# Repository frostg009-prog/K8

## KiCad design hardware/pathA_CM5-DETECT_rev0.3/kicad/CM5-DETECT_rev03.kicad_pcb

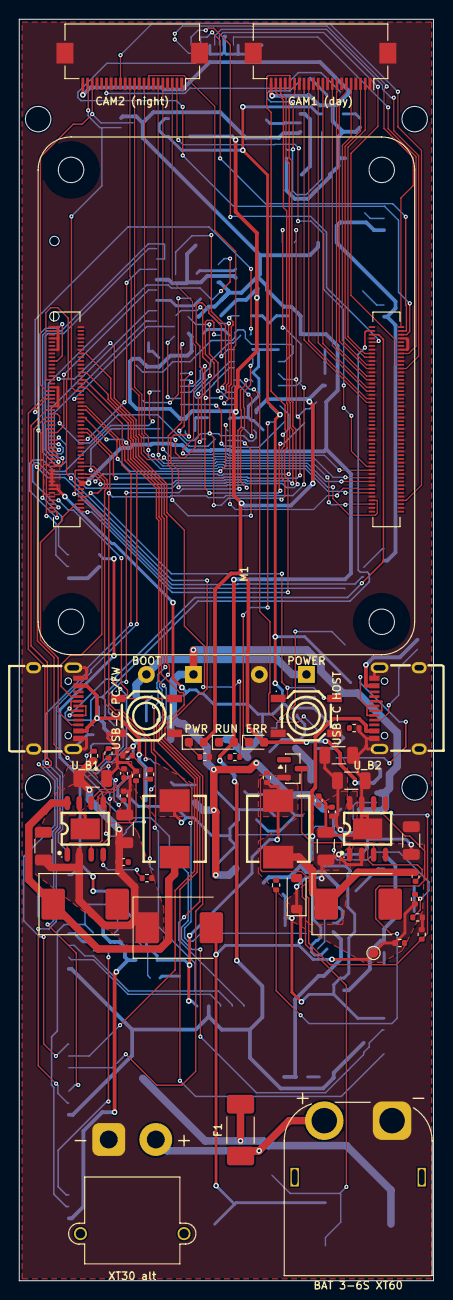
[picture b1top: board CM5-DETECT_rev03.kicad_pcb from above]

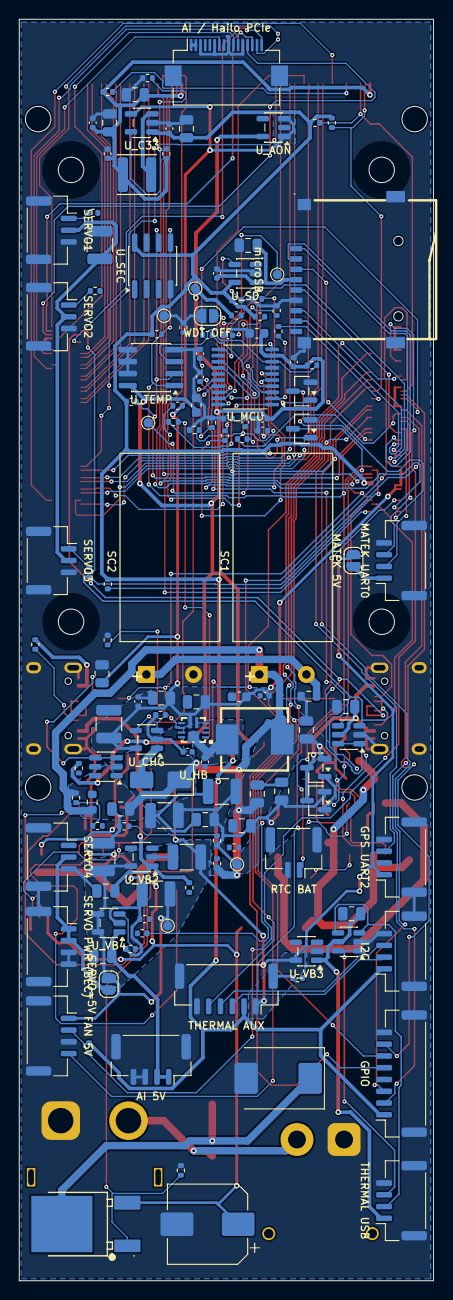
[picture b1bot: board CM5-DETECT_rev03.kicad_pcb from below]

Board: 4 copper layers, 44.0 x 134.0 mm, 194 parts (139 on the bottom side), 158 nets.

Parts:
AI 5V: AI POWER 5V (5V,5V,GND,GND) for Hailo HA; JST_GH_SM04B-GHS-TB_1x04-1MP_P1.25mm_Horizontal
AI / Hailo PCIe: PCIe x1 FFC 16p (Pi 5 pinout) -> Hailo A; Hirose_FH12-16S-0.5SH_1x16-1MP_P0.50mm_Horizontal
BAT 3-6S XT60: XT60PW-M (battery 3S-6S); AMASS_XT60PW-M_1x02_P7.20mm_Horizontal
BOOT: BOOT (nRPIBOOT); SW-SMD_4P-L5.2-W5.2-P3.70-LS6.4
C1, C2, C3, C4, C30, C31, C32, C33, C40, C42, C44: 22uF; C_0805_2012Metric
C5, C6, C9, C13, C16, C23, C26, C35, C46, C47, C49, C50, C52, C53, C54: 100nF; C_0402_1005Metric
C7, C39, C41, C43, C45, C48: 10uF; C_0805_2012Metric
C8, C10, C11, C12, C20, C21, C22: 2.2uF 100V; C_1206_3216Metric
C14, C24: 8.2nF; C_0402_1005Metric
C15, C25: 100pF; C_0402_1005Metric
C17, C18, C19, C27, C28, C29, C55: 47uF 16V; C_1210_3225Metric
C34: 2.2uF; C_0402_1005Metric
C36: 4.7nF; C_0402_1005Metric
C37, C38, C51: 1uF; C_0603_1608Metric
CAM1 (day): CAM1 MIPI CSI-2 4-lane FFC 22p 0.5mm (Pi; Hirose_FH12-22S-0.5SH_1x22-1MP_P0.50mm_Horizontal
CAM2 (night): CAM2 MIPI CSI-2 4-lane FFC 22p 0.5mm (Pi; Hirose_FH12-22S-0.5SH_1x22-1MP_P0.50mm_Horizontal
C_BULK: 100uF 50V low-ESR; CP_Elec_8x10
D_B1, D_B2: SS510C 5A 100V Schottky; D_SMC
D_B1IN: SS510C (blocks hold-up back-feed); D_SMC
D_CHG: SS34 (cap max 4.8 V = 2.4 V/cell); D_SMA
D_RPZ: BZT52C12 Vgs clamp; D_SOD-123
D_TVS: SMCJ33A TVS 1.5kW; D_SMC
ERR: LED red ERROR; LED_0603_1608Metric
F1: 10A fast 2410 125V; Fuse_2410
FAN 5V: FAN 5V PWM (5V,PWM,GND,TACH); JST_GH_SM04B-GHS-TB_1x04-1MP_P1.25mm_Horizontal
GPIO: GPIO (3V3,G7,G10,G11,G16,G17,G24,GND); JST_GH_SM08B-GHS-TB_1x08-1MP_P1.25mm_Horizontal
GPS UART2: GPS/TELEM UART2 (5V,TX,RX,GND); JST_GH_SM04B-GHS-TB_1x04-1MP_P1.25mm_Horizontal
H1, H2, H3, H4: M2.5; MountingHole_2.7mm_M2.5
I2C: I2C1 (3V3,SCL,SDA,GND); JST_GH_SM04B-GHS-TB_1x04-1MP_P1.25mm_Horizontal
L_B1, L_B2: 6.8uH 6A FXL0630-6R8-M; IND-SMD_L7.0-W6.6
L_C33: 2.2uH 2.3A FNR4012S2R2MT; L_Changjiang_FNR4012S
L_HB: 2.2uH 9.5A SLO0650H2R2MTT; IND-SMD_L7.1-W6.6_SLO0650H
M1: Raspberry Pi CM5 (CM5108032 / CM5116032; Raspberry-Pi-5-Compute-Module
MATEK 5V: close = 5V to Matek pin1; SolderJumper-2_P1.3mm_Open_RoundedPad1.0x1.5mm
MATEK UART0: MATEK UART0 (5V*,TX,RX,GND); JST_GH_SM04B-GHS-TB_1x04-1MP_P1.25mm_Horizontal
POWER: POWER (PWR_BUT); SW-SMD_4P-L5.2-W5.2-P3.70-LS6.4
PWR: LED green PWR; LED_0603_1608Metric
Q_AUX_OFF: 2N7002; SOT-23
Q_PMIC: 2N7002 -> CM5 PMIC_EN (hard reset); SOT-23
Q_PWB: 2N7002 -> CM5 PWR_BUT (wake / clean off); SOT-23
Q_RP: NCE60P12K P-MOS 60V reverse-polarity; TO-252-2_L6.5-W6.1-P4.58-LS10.0-TL
R1: 47k; R_0402_1005Metric
R2, R4, R10, R16, R18, R25, R49, R50: 100k; R_0402_1005Metric
R3, R9, R15, R27, R36, R42, R43, R44, R45, R46, R47, R48, R56: 10k; R_0402_1005Metric
R5, R11: 18k; R_0402_1005Metric
R6, R12: 249k; R_0402_1005Metric
R7, R13: 10.5k; R_0402_1005Metric
R8, R14: 53.6k; R_0402_1005Metric
R17, R30, R31: 6.8k; R_0402_1005Metric
R19, R20: 10k; R_0603_1608Metric
R21: 340k; R_0402_1005Metric
R22: 107k; R_0402_1005Metric
R23: 30k; R_0402_1005Metric
R24: 127k; R_0402_1005Metric
R26: 45.3k; R_0402_1005Metric
R28, R29: 56k; R_0402_1005Metric
R32: 3.4k; R_0402_1005Metric
R33, R34, R35, R51, R52: 2.2k; R_0402_1005Metric
R37, R38, R39, R40, R41, R53, R55: 1k; R_0402_1005Metric
R54, R57, R58, R59, R60: 220R; R_0402_1005Metric
RTC BAT: RTC battery 3V (+,-); JST_GH_SM02B-GHS-TB_1x02-1MP_P1.25mm_Horizontal
RUN: LED blue RUN; LED_0603_1608Metric
R_VREF: 0R; R_0402_1005Metric
SC1: 10F 2.7V supercap (Jianghai SCCDQR2R7106; SuperCap_D10_L20_Horizontal
SC2: 10F 2.7V supercap; SuperCap_D10_L20_Horizontal
SERVO1: SERVO1 (SIG,V+,GND); JST_GH_SM03B-GHS-TB_1x03-1MP_P1.25mm_Horizontal
SERVO2: SERVO2 (SIG,V+,GND); JST_GH_SM03B-GHS-TB_1x03-1MP_P1.25mm_Horizontal
SERVO3: SERVO3 (SIG,V+,GND); JST_GH_SM03B-GHS-TB_1x03-1MP_P1.25mm_Horizontal
SERVO4: SERVO4 (SIG,V+,GND); JST_GH_SM03B-GHS-TB_1x03-1MP_P1.25mm_Horizontal
SERVO PWR (BEC): SERVO POWER IN from BEC (V+,V+,GND,GND); JST_GH_SM04B-GHS-TB_1x04-1MP_P1.25mm_Horizontal
SERVO=5V: close = servos from 5V_AUX (<=1.5 A tota; SolderJumper-2_P1.3mm_Open_RoundedPad1.0x1.5mm
THERMAL AUX: THERMAL AUX (5V,3V3,SCL,SDA,SYNC,GND); JST_GH_SM06B-GHS-TB_1x06-1MP_P1.25mm_Horizontal
THERMAL USB: THERMAL USB (VBUS,D-,D+,GND); JST_GH_SM04B-GHS-TB_1x04-1MP_P1.25mm_Horizontal
TP_3V3: 3V3; TestPoint_Pad_D1.0mm
TP_5V: 5V; TestPoint_Pad_D1.0mm
TP_5VA: 5VA; TestPoint_Pad_D1.0mm
TP_GND: GND; TestPoint_Pad_D1.0mm
TP_RST: RST; TestPoint_Pad_D1.0mm
TP_SWIO: SWIO; TestPoint_Pad_D1.0mm
TP_VIN: VIN; TestPoint_Pad_D1.0mm
USB-C HOST: USB-C #2 HOST; USB-C-SMD_TYPE-C-16PIN-2MD-073
USB-C PC/FW: USB-C #1 FW/PC (rpiboot + USB gadget); USB-C-SMD_TYPE-C-16PIN-2MD-073
U_AON: ME6211C33M5G LDO 3.3V; SOT-23-5
U_B1, U_B2: RT6365GSP 60V 5A buck (alt SCT2650STER); SOP-8_L5.0-W3.9-P1.27-LS6.0-BL-EP
U_C33: SY8089A1AAC 2A buck 3.3V cameras; SOT-23-5
U_CHG: SY6280AAC supercap charger 1A; SOT-23-5
U_ESD1, U_ESD2, U_ESD3: USBLC6-2SC6 ESD; SOT-23-6
U_HB: SGM6611C boost 7A (hold-up 5.03 V); VQFN-11_L2.5-W2.0-P0.50-TL_TI_RNR
U_ID1, U_ID2: CH213K ideal diode VBUS1->5V; SOT-23
U_MCU: CH32V003F4P6 supervisor (HW watchdog, po; TSSOP-20_4.4x6.5mm_P0.65mm
U_SD: RT9742GGJ5 SD power switch; TSOT-23-5
U_SEC: ATECC608B secure element (I2C 0x60); SOIC-8_3.9x4.9mm_P1.27mm
U_TEMP: NST175H temp sensor 0x48; SOIC-8_3.9x4.9mm_P1.27mm
U_VB2, U_VB3: SY6280AAC VBUS switch 1A; SOT-23-5
U_VB4: SY6280AAC 5V for AI board 2A; SOT-23-5
WDT OFF: close = watchdog disabled (bench); SolderJumper-2_P1.3mm_Open_RoundedPad1.0x1.5mm
XT30 alt: XT30PW-M (alternative input); AMASS_XT30PW-M_1x02_P2.50mm_Horizontal
microSD: microSD push-push TF-01A; TF-SMD_TF-01A

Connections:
+3V3_AON: C38.1, C50.1, C51.1, C53.1, ERR.2, PWR.2, R18.2, R43.2, R44.2, TP_3V3.1, U_AON.5, U_MCU.9, U_TEMP.8
+3V3_CAM: C40.1, C45.1, C46.1, C47.1, CAM1 (day).22, CAM2 (night).22, L_C33.2, R26.1, R33.2
+3V3_CM5: C7.1, C54.1, GPIO.1, I2C.1, M1.84, M1.86, R34.2, R35.2, R36.2, R42.2, R51.2, R52.2, R56.2, RUN.2, R_VREF.2, THERMAL AUX.2, U_C33.1, U_SD.5, U_SEC.8
+5V_AI: AI 5V.1, AI 5V.2, AI / Hailo PCIe.1, AI / Hailo PCIe.2, C44.1, U_VB4.1
+5V_AUX: C27.1, C28.1, C29.1, FAN 5V.1, GPS UART2.1, L_B2.2, MATEK 5V.2, R14.1, SERVO=5V.2, THERMAL AUX.1, TP_5VA.1, U_VB2.5, U_VB3.5, U_VB4.4, U_VB4.5
+5V_CM5: C1.1, C2.1, C3.1, C4.1, C5.1, C6.1, C17.1, C18.1, C19.1, C32.1, C33.1, C37.1, C39.1, L_B1.2, M1.77, M1.79, M1.81, M1.83, M1.85, M1.87, R8.1, R21.1, R45.1, TP_5V.1, U_AON.1, U_AON.3, U_C33.4, U_CHG.5, U_HB.6, U_ID1.2, U_ID2.2
AUX_OFF: Q_AUX_OFF.1, R16.1, U_MCU.17
B1_BOOT: C16.1, U_B1.1
B1_CC: C14.1, R7.2
B1_COMP: C15.1, R7.1, U_B1.6
B1_EN: R4.2, R5.1, U_B1.3
B1_FB: R8.2, R9.1, U_B1.5
B1_RT: R6.1, U_B1.4
B1_SW: C16.2, D_B1.1, L_B1.1, U_B1.8
B2_BOOT: C26.1, U_B2.1
B2_CC: C24.1, R13.2
B2_COMP: C25.1, R13.1, U_B2.6
B2_EN: Q_AUX_OFF.3, R10.2, R11.1, U_B2.3
B2_FB: R14.2, R15.1, U_B2.5
B2_RT: R12.1, U_B2.4
B2_SW: C26.2, D_B2.1, L_B2.1, U_B2.8
C33_FB: R26.2, R27.1, U_C33.5
C33_LX: L_C33.1, U_C33.3
CAM1_C_N: CAM1 (day).8, M1.127
CAM1_C_P: CAM1 (day).9, M1.129
CAM1_D0_N: CAM1 (day).2, M1.115
CAM1_D0_P: CAM1 (day).3, M1.117
CAM1_D1_N: CAM1 (day).5, M1.121
CAM1_D1_P: CAM1 (day).6, M1.123
CAM1_D2_N: CAM1 (day).11, M1.133
CAM1_D2_P: CAM1 (day).12, M1.135
CAM1_D3_N: CAM1 (day).14, M1.139
CAM1_D3_P: CAM1 (day).15, M1.141
CAM1_GPIO0: CAM1 (day).17, M1.97
CAM1_GPIO1: CAM1 (day).18, M1.100
CAM1_SCL: CAM1 (day).20, M1.80
CAM1_SDA: CAM1 (day).21, M1.82
CAM2_C_N: CAM2 (night).8, M1.187
CAM2_C_P: CAM2 (night).9, M1.189
CAM2_D0_N: CAM2 (night).2, M1.175
CAM2_D0_P: CAM2 (night).3, M1.177
CAM2_D1_N: CAM2 (night).5, M1.181
CAM2_D1_P: CAM2 (night).6, M1.183
CAM2_D2_N: CAM2 (night).11, M1.193
CAM2_D2_P: CAM2 (night).12, M1.195
CAM2_D3_N: CAM2 (night).14, M1.194
CAM2_D3_P: CAM2 (night).15, M1.196
CAM2_EN: CAM2 (night).17, R33.1
CAM2_SCL: CAM2 (night).20, M1.35, R34.1
CAM2_SDA: CAM2 (night).21, M1.36, R35.1
CHG_ISET: R17.1, U_CHG.3
CM5_ON_SENSE: R42.1, U_MCU.19
FAN_PWM: FAN 5V.2, M1.19, R56.1
FAN_TACH: FAN 5V.4, M1.16
GND: AI 5V.3, AI 5V.4, AI 5V.MP, AI / Hailo PCIe.3, AI / Hailo PCIe.6, AI / Hailo PCIe.9, AI / Hailo PCIe.12, AI / Hailo PCIe.MP, BAT 3-6S XT60.1, BOOT.3, BOOT.4, C1.2, C2.2, C3.2, C4.2, C5.2, C6.2, C7.2, C8.2, C9.2, C10.2, C11.2, C12.2, C13.2, C14.2, C15.2, C17.2, C18.2, C19.2, C20.2, C21.2, C22.2, C23.2, C24.2, C25.2, C27.2, C28.2, C29.2, C30.2, C31.2, C32.2, C33.2, C34.2, C36.2, C37.2, C38.2, C39.2, C40.2, C41.2, C42.2, C43.2, C44.2, C45.2, C46.2, C47.2, C48.2, C49.2, C50.2, C51.2, C52.2, C53.2, C54.2, C55.2, CAM1 (day).1, CAM1 (day).4, CAM1 (day).7, CAM1 (day).10, CAM1 (day).13, CAM1 (day).16, CAM1 (day).19, CAM1 (day).MP, CAM2 (night).1, CAM2 (night).4, CAM2 (night).7, CAM2 (night).10, CAM2 (night).13, CAM2 (night).16, CAM2 (night).19, CAM2 (night).MP, C_BULK.2, D_B1.2, D_B2.2, D_TVS.2, FAN 5V.3, FAN 5V.MP, GPIO.8, GPIO.MP, GPS UART2.4, GPS UART2.MP, I2C.4, I2C.MP, M1.1, M1.2, M1.7, M1.8, M1.13, M1.14, M1.22, M1.23, M1.32, M1.33, M1.42, M1.43, M1.52, M1.53, M1.59, M1.60, M1.65, M1.66, M1.71, M1.74, M1.98, M1.107, M1.108, M1.113, M1.114, M1.119, M1.120, M1.125, M1.126, M1.131, M1.132, M1.137, M1.138, M1.144, M1.150, M1.155, M1.156, M1.161, M1.162, M1.167, M1.168, M1.173, M1.174, M1.179, M1.180, M1.185, M1.186, M1.191, M1.192, M1.197, M1.198, MATEK UART0.4, MATEK UART0.MP, POWER.3, POWER.4, Q_AUX_OFF.2, Q_PMIC.2, Q_PWB.2, R1.2, R3.2, R5.2, R6.2, R9.2, R11.2, R12.2, R15.2, R16.2, R17.2, R20.2, R22.2, R24.2, R27.2, R30.2, R31.2, R32.2, R46.2, R48.2, R49.2, R50.2, R53.2, RTC BAT.2, RTC BAT.MP, SC2.2, SERVO1.3, SERVO1.MP, SERVO2.3, SERVO2.MP, SERVO3.3, SERVO3.MP, SERVO4.3, SERVO4.MP, SERVO PWR (BEC).3, SERVO PWR (BEC).4, SERVO PWR (BEC).MP, THERMAL AUX.6, THERMAL AUX.MP, THERMAL USB.4, THERMAL USB.MP, TP_GND.1, USB-C HOST.13, USB-C HOST.14, USB-C HOST.A1B12, USB-C HOST.B1A12, USB-C PC/FW.13, USB-C PC/FW.14, USB-C PC/FW.A1B12, USB-C PC/FW.B1A12, U_AON.2, U_B1.7, U_B1.9, U_B2.7, U_B2.9, U_C33.2, U_CHG.2, U_ESD1.2, U_ESD2.2, U_ESD3.2, U_HB.5, U_ID1.1, U_ID2.1, U_MCU.7, U_SD.2, U_SEC.4, U_TEMP.4, U_TEMP.5, U_TEMP.6, U_TEMP.7, U_VB2.2, U_VB3.2, U_VB4.2, WDT OFF.2, XT30 alt.1, microSD.6, microSD.10, microSD.11, microSD.12, microSD.13
GPIO_VREF: M1.78, R_VREF.1
HB_BOOT: C35.1, U_HB.10
HB_CC: C36.1, R23.2
HB_COMP: R23.1, U_HB.4
HB_FB: R21.2, R22.1, U_HB.3
HB_ILIM: R24.1, U_HB.8
HB_SW: C35.2, L_HB.2, U_HB.11
HB_VCC: C34.1, U_HB.2
HEARTBEAT: M1.46, R39.2
HEARTBEAT_R: R39.1, U_MCU.10
HOLD_EN: R25.1, R41.2, U_HB.7
HOLD_EN_R: R41.1, U_MCU.15
I2C1_SCL: I2C.2, M1.56, R52.1, THERMAL AUX.3, U_SEC.6, U_TEMP.2
I2C1_SDA: I2C.3, M1.58, R51.1, THERMAL AUX.4, U_SEC.5, U_TEMP.1
IO_GPIO7: GPIO.2, M1.37
IO_GPIO10: GPIO.3, M1.44
IO_GPIO11: GPIO.4, M1.38
IO_GPIO16: GPIO.5, M1.29
IO_GPIO17: GPIO.6, M1.50
IO_GPIO24: GPIO.7, M1.45
LEDE_K: ERR.1, R55.1
LEDP_K: PWR.1, R53.1
LEDR_K: R54.1, RUN.1
LED_ERR_N: R55.2, U_MCU.1
LED_RUN_N: M1.27, R54.2
MATEK_5V: MATEK 5V.1, MATEK UART0.1
MCU_NRST: R43.1, TP_RST.1, U_MCU.4
MCU_RX: M1.39, R38.2
MCU_RX_R: R38.1, U_MCU.3
MCU_SWIO: TP_SWIO.1, U_MCU.18
MCU_TX: M1.40, R37.2
MCU_TX_R: R37.1, U_MCU.2
NRPIBOOT: BOOT.1, BOOT.2, M1.93
PCIE_CLKREQ_N: AI / Hailo PCIe.15, M1.102
PCIE_CLK_N: AI / Hailo PCIe.5, M1.112
PCIE_CLK_P: AI / Hailo PCIe.4, M1.110
PCIE_DET_WAKE: AI / Hailo PCIe.14, M1.104
PCIE_PWR_EN: AI / Hailo PCIe.13, M1.106
PCIE_RST_N: AI / Hailo PCIe.16, M1.109
PCIE_RX_N: AI / Hailo PCIe.8, M1.118
PCIE_RX_P: AI / Hailo PCIe.7, M1.116
PCIE_TX_N: AI / Hailo PCIe.11, M1.124
PCIE_TX_P: AI / Hailo PCIe.10, M1.122
PFAIL_N: M1.47, R40.2
PFAIL_R: R40.1, U_MCU.11
PMIC_EN: M1.99, Q_PMIC.3
PMIC_OFF: Q_PMIC.1, R49.1, U_MCU.12
PWRBTN_PRESS: Q_PWB.1, R50.1, U_MCU.13
PWR_BUT: M1.92, POWER.1, POWER.2, Q_PWB.3
QRP_G: D_RPZ.2, Q_RP.1, R1.1
SCAP_CHG: D_CHG.2, U_CHG.1
SCAP_CHG_EN: R18.1, U_CHG.4, U_MCU.16
SCAP_MID: R19.2, R20.1, SC1.2, SC2.1
SD_CLK: M1.57, microSD.5
SD_CMD: M1.62, microSD.3
SD_D0: M1.63, microSD.7
SD_D1: M1.67, microSD.8
SD_D2: M1.69, microSD.1
SD_D3: M1.61, microSD.2
SD_PWR_ON: M1.75, R36.1, U_SD.4
SD_VDD: C48.1, C49.1, U_SD.1, microSD.4
SERVO1: R57.2, SERVO1.1
SERVO1_G: M1.31, R57.1
SERVO2: R58.2, SERVO2.1
SERVO2_G: M1.28, R58.1
SERVO3: R59.2, SERVO3.1
SERVO3_G: M1.49, R59.1
SERVO4: R60.2, SERVO4.1
SERVO4_G: M1.26, R60.1
TEMP_ALERT: R44.1, U_MCU.8, U_TEMP.3
THU_DN: M1.165, THERMAL USB.2, U_ESD3.3, U_ESD3.4
THU_DP: M1.163, THERMAL USB.3, U_ESD3.1, U_ESD3.6
TH_SYNC: M1.30, THERMAL AUX.5
UART0_RX: M1.51, MATEK UART0.3
UART0_TX: M1.55, MATEK UART0.2
UART2_RX: GPS UART2.3, M1.34
UART2_TX: GPS UART2.2, M1.54
USB1_CC1: M1.94, USB-C PC/FW.A5
USB1_CC2: M1.96, USB-C PC/FW.B5
USB1_DN: M1.103, USB-C PC/FW.A7, USB-C PC/FW.B7, U_ESD1.3, U_ESD1.4
USB1_DP: M1.105, USB-C PC/FW.A6, USB-C PC/FW.B6, U_ESD1.1, U_ESD1.6
USB2_CC1: R28.1, USB-C HOST.A5
USB2_CC2: R29.1, USB-C HOST.B5
USB2_DN: M1.136, USB-C HOST.A7, USB-C HOST.B7, U_ESD2.3, U_ESD2.4
USB2_DP: M1.134, USB-C HOST.A6, USB-C HOST.B6, U_ESD2.1, U_ESD2.6
V5_SENSE: C52.1, R45.2, R46.1, U_MCU.6
VB2_ISET: R30.1, U_VB2.3
VB3_ISET: R31.1, U_VB3.3
VB4_ISET: R32.1, U_VB4.3
VBAT_F: D_TVS.1, F1.2, Q_RP.4
VBAT_RAW: BAT 3-6S XT60.2, F1.1, XT30 alt.2
VBAT_RTC: M1.76, RTC BAT.1
VBAT_SENSE: C9.1, R2.2, R3.1, U_MCU.5
VBUS1: C41.1, USB-C PC/FW.A4B9, USB-C PC/FW.B4A9, U_ESD1.5, U_ID1.3, U_ID2.3
VBUS2: C42.1, R28.2, R29.2, USB-C HOST.A4B9, USB-C HOST.B4A9, U_ESD2.5, U_VB2.1
VBUS3: C43.1, THERMAL USB.1, U_ESD3.5, U_VB3.1
VBUS_EN: M1.111, U_VB2.4, U_VB3.4
VIN_B1: C10.1, C11.1, C12.1, C13.1, D_B1IN.1, R4.1, U_B1.2
VIN_PROT: C8.1, C20.1, C21.1, C22.1, C23.1, C_BULK.1, D_B1IN.2, D_RPZ.1, Q_RP.3, R2.1, R10.1, TP_VIN.1, U_B2.2
VSCAP: C30.1, C31.1, D_CHG.1, L_HB.1, R19.1, R25.2, R47.1, SC1.1, U_HB.9
VSCAP_SENSE: R47.2, R48.1, U_MCU.14
VSERVO: C55.1, SERVO1.2, SERVO2.2, SERVO3.2, SERVO4.2, SERVO PWR (BEC).1, SERVO PWR (BEC).2, SERVO=5V.1
WDT_DIS: U_MCU.20, WDT OFF.1

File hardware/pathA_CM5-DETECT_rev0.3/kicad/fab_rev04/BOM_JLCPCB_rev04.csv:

Comment,Designator,Footprint,LCSC Part #
22uF,"C1,C2,C3,C4,C30,C31,C32,C33,C40,C42,C44",C_0805_2012Metric,C45783
100nF,"C5,C6,C9,C13,C16,C23,C26,C35,C46,C47,C49,C50,C52,C53,C54",C_0402_1005Metric,C1525
10uF,"C7,C39,C41,C43,C45,C48",C_0805_2012Metric,C15850
2.2uF 100V,"C8,C10,C11,C12,C20,C21,C22",C_1206_3216Metric,C170101
8.2nF,"C14,C24",C_0402_1005Metric,C45186
100pF,"C15,C25",C_0402_1005Metric,C1546
47uF 16V,"C17,C18,C19,C27,C28,C29,C55",C_1210_3225Metric,C77101
2.2uF,C34,C_0402_1005Metric,C12530
4.7nF,C36,C_0402_1005Metric,C1538
1uF,"C37,C38,C51",C_0603_1608Metric,C15849
100uF 50V low-ESR,C_BULK,CP_Elec_8x10,C48935390
SS510C (blocks hold-up back-feed),D_B1IN,D_SMC,C19229
SS510C 5A 100V Schottky,"D_B1,D_B2",D_SMC,C19229
SS34 (cap max 4.8 V = 2.4 V/cell),D_CHG,D_SMA,C8678
LED red ERROR,D_ERR,LED_0603_1608Metric,C2286
LED green PWR,D_PWR,LED_0603_1608Metric,C12624
BZT52C12 Vgs clamp,D_RPZ,D_SOD-123,C43491
LED blue RUN,D_RUN,LED_0603_1608Metric,C2288
SMCJ33A TVS 1.5kW,D_TVS,D_SMC,C152083
10A fast 2410 125V,F1,Fuse_2410,C2838934
"AI POWER 5V (5V,5V,GND,GND) for Hailo HAT",J_AIPWR,JST_SH_SM04B-SRSS-TB_1x04-1MP_P1.00mm_Horizontal,C160404
XT60PW-M (battery 3S-6S),J_BAT,AMASS_XT60PW-M_1x02_P7.20mm_Horizontal,C98732
CAM1 MIPI CSI-2 4-lane FFC 22p 0.5mm (Pi 5 / CM5IO pinout),J_CAM1,Hirose_FH12-22S-0.5SH_1x22-1MP_P0.50mm_Horizontal,C597981
CAM2 MIPI CSI-2 4-lane FFC 22p 0.5mm (Pi 5 / CM5IO pinout),J_CAM2,Hirose_FH12-22S-0.5SH_1x22-1MP_P0.50mm_Horizontal,C597981
"FAN 5V PWM (5V,PWM,GND,TACH)",J_FAN,JST_SH_SM04B-SRSS-TB_1x04-1MP_P1.00mm_Horizontal,C160404
"GPS/TELEM UART2 (5V,TX,RX,GND)",J_GPS,JST_SH_SM04B-SRSS-TB_1x04-1MP_P1.00mm_Horizontal,C160404
"I2C1 (3V3,SCL,SDA,GND)",J_I2C,JST_SH_SM04B-SRSS-TB_1x04-1MP_P1.00mm_Horizontal,C160404
"GPIO (3V3,G7,G10,G11,G16,G17,G24,GND)",J_IO,JST_SH_SM08B-SRSS-TB_1x08-1MP_P1.00mm_Horizontal,C160408
"MATEK UART0 (5V*,TX,RX,GND)",J_MATEK,JST_SH_SM04B-SRSS-TB_1x04-1MP_P1.00mm_Horizontal,C160404
PCIe x1 FFC 16p (Pi 5 pinout) -> Hailo AI HAT+/M.2 HAT+,J_PCIE,Hirose_FH12-16S-0.5SH_1x16-1MP_P0.50mm_Horizontal,C596731
"RTC battery 3V (+,-)",J_RTC,JST_SH_SM02B-SRSS-TB_1x02-1MP_P1.00mm_Horizontal,C160402
"SERVO1 (SIG,V+,GND)",J_S1,JST_SH_SM03B-SRSS-TB_1x03-1MP_P1.00mm_Horizontal,C160403
"SERVO2 (SIG,V+,GND)",J_S2,JST_SH_SM03B-SRSS-TB_1x03-1MP_P1.00mm_Horizontal,C160403
"SERVO3 (SIG,V+,GND)",J_S3,JST_SH_SM03B-SRSS-TB_1x03-1MP_P1.00mm_Horizontal,C160403
"SERVO4 (SIG,V+,GND)",J_S4,JST_SH_SM03B-SRSS-TB_1x03-1MP_P1.00mm_Horizontal,C160403
microSD push-push TF-01A,J_SD,TF-SMD_TF-01A,C91145
"SERVO POWER IN from BEC (V+,V+,GND,GND)",J_SPWR,JST_SH_SM04B-SRSS-TB_1x04-1MP_P1.00mm_Horizontal,C160404
"THERMAL AUX (5V,3V3,SCL,SDA,SYNC,GND)",J_THA,JST_SH_SM06B-SRSS-TB_1x06-1MP_P1.00mm_Horizontal,C160406
"THERMAL USB (VBUS,D-,D+,GND)",J_THU,JST_SH_SM04B-SRSS-TB_1x04-1MP_P1.00mm_Horizontal,C160404
USB-C #1 FW/PC (rpiboot + USB gadget),J_USB1,USB-C-SMD_TYPE-C-16PIN-2MD-073,C2765186
USB-C #2 HOST,J_USB2,USB-C-SMD_TYPE-C-16PIN-2MD-073,C2765186
6.8uH 6A FXL0630-6R8-M,"L_B1,L_B2",IND-SMD_L7.0-W6.6,C167221
2.2uH 2.3A FNR4012S2R2MT,L_C33,L_Changjiang_FNR4012S,C167776
2.2uH 9.5A SLO0650H2R2MTT,L_HB,IND-SMD_L7.1-W6.6_SLO0650H,C216163
Raspberry Pi CM5 (CM5108032 / CM5116032 / Lite),M1,Raspberry-Pi-5-Compute-Module,
2N7002,Q_AUX_OFF,SOT-23,C8545
2N7002 -> CM5 PMIC_EN (hard reset),Q_PMIC,SOT-23,C8545
2N7002 -> CM5 PWR_BUT (wake / clean off),Q_PWB,SOT-23,C8545
NCE60P12K P-MOS 60V reverse-polarity,Q_RP,TO-252-2_L6.5-W6.1-P4.58-LS10.0-TL,C326372
47k,R1,R_0402_1005Metric,C25792
100k,"R2,R4,R10,R16,R18,R25,R49,R50",R_0402_1005Metric,C25741
10k,"R3,R9,R15,R27,R36,R42,R43,R44,R45,R46,R47,R48,R56",R_0402_1005Metric,C25744
18k,"R5,R11",R_0402_1005Metric,C25762
249k,"R6,R12",R_0402_1005Metric,C2998084
10.5k,"R7,R13",R_0402_1005Metric,C25850
53.6k,"R8,R14",R_0402_1005Metric,C5153961
6.8k,"R17,R30,R31",R_0402_1005Metric,C93940
10k,"R19,R20",R_0603_1608Metric,C25804
340k,R21,R_0402_1005Metric,C2933090
107k,R22,R_0402_1005Metric,C25743
30k,R23,R_0402_1005Metric,C25776
127k,R24,R_0402_1005Metric,C25751
45.3k,R26,R_0402_1005Metric,C2933099
56k,"R28,R29",R_0402_1005Metric,C25796
3.4k,R32,R_0402_1005Metric,C4940
2.2k,"R33,R34,R35",R_0402_1005Metric,C25879
1k,"R37,R38,R39,R40,R41,R53,R55",R_0402_1005Metric,C11702
220R,"R54,R57,R58,R59,R60",R_0402_1005Metric,C25091
0R,R_VREF,R_0402_1005Metric,C17168
10F 2.7V supercap (Jianghai SCCDQR2R7106 / Kamcap),SC1,SuperCap_D10_L20_Horizontal,
10F 2.7V supercap,SC2,SuperCap_D10_L20_Horizontal,
BOOT (nRPIBOOT),SW_BOOT,SW-SMD_4P-L5.2-W5.2-P3.70-LS6.4,C42420254
POWER (PWR_BUT),SW_PWR,SW-SMD_4P-L5.2-W5.2-P3.70-LS6.4,C42420254
ME6211C33M5G LDO 3.3V,U_AON,SOT-23-5,C82942
RT6365GSP 60V 5A buck (alt SCT2650STER),"U_B1,U_B2",SOP-8_L5.0-W3.9-P1.27-LS6.0-BL-EP,C3024482
SY8089A1AAC 2A buck 3.3V cameras,U_C33,SOT-23-5,C479074
SY6280AAC supercap charger 1A,U_CHG,SOT-23-5,C55136
USBLC6-2SC6 ESD,"U_ESD1,U_ESD2,U_ESD3",SOT-23-6,C2827654
SGM6611C boost 7A (hold-up 5.03 V),U_HB,VQFN-11_L2.5-W2.0-P0.50-TL_TI_RNR,C699669
CH213K ideal diode VBUS1->5V,"U_ID1,U_ID2",SOT-23,C5456874
"CH32V003F4P6 supervisor (HW watchdog, power-fail)",U_MCU,TSSOP-20_4.4x6.5mm_P0.65mm,C5187096
RT9742GGJ5 SD power switch,U_SD,TSOT-23-5,C250547
ATECC608B secure element (I2C 0x60),U_SEC,SOIC-8_3.9x4.9mm_P1.27mm,C1518769
NST175H temp sensor 0x48,U_TEMP,SOIC-8_3.9x4.9mm_P1.27mm,C917444
SY6280AAC VBUS switch 1A,"U_VB2,U_VB3",SOT-23-5,C55136
SY6280AAC 5V for AI board 2A,U_VB4,SOT-23-5,C55136
